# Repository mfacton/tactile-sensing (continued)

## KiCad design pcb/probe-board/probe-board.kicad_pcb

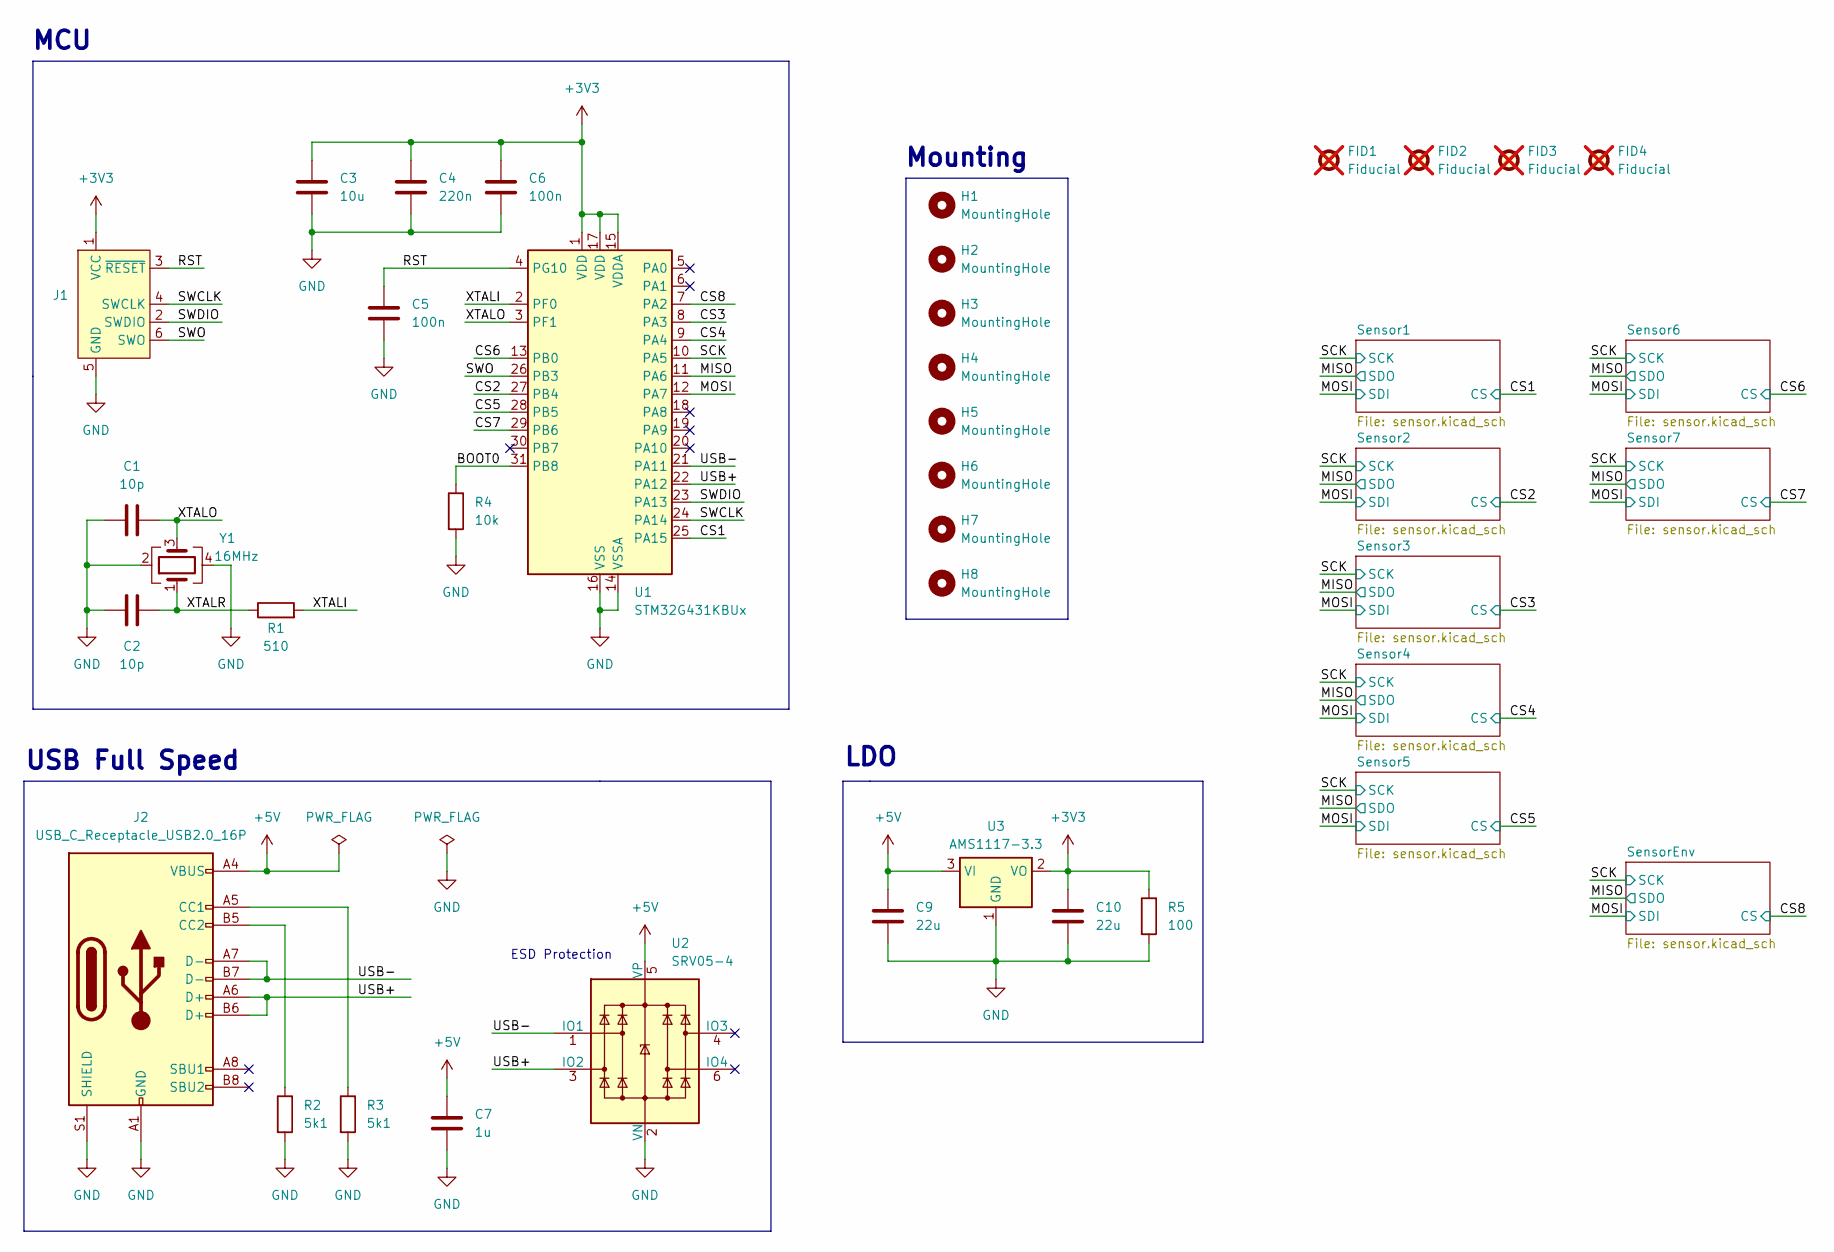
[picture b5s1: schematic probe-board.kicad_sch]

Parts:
C1, C2: 10p; C_0402_1005Metric; LCSC C32949
C3: 10u; C_0402_1005Metric; LCSC C15525
C4: 220n; C_0402_1005Metric; LCSC C16772
C5, C6: 100n; C_0402_1005Metric; LCSC C1525
C7: 1u; C_0402_1005Metric; LCSC C52923
C9: 22u; C_0805_2012Metric; LCSC C45783
C10: 22u; C_0603_1608Metric; LCSC C59461
FID1, FID2, FID3, FID4: Fiducial; Fiducial_1mm_Mask2mm; not fitted
H1, H2, H3, H4, H5, H6, H7, H8: MountingHole; MountingHole_3.2mm_M3
J1: Conn_ARM_SWD_TagConnect_TC2030-NL; Tag-Connect_TC2030-IDC-NL_2x03_P1.27mm_Vertical
J2: USB_C_Receptacle_USB2.0_16P; USB_C_Receptacle_GCT_USB4105-xx-A_16P_TopMnt_Horizontal; LCSC C2765186
R1: 510; R_0402_1005Metric; LCSC C25123
R2, R3: 5k1; R_0402_1005Metric; LCSC C25905
R4: 10k; R_0402_1005Metric; LCSC C25744
R5: 100; R_0805_2012Metric; LCSC C17408
U1: STM32G431KBUx; QFN-32-1EP_5x5mm_P0.5mm_EP3.45x3.45mm; LCSC C1341901
U2: SRV05-4; SOT-23-6; LCSC C7420376
U3: AMS1117-3.3; SOT-223-3_TabPin2; LCSC C6186
Y1: 16MHz; Crystal_SMD_3225-4Pin_3.2x2.5mm; LCSC C13738

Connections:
+3V3: C3.1, C4.1, C6.1, C10.1, J1.1 (VCC), R5.1, U1.1 (VDD), U1.15 (VDDA), U1.17 (VDD), U3.2 (VO); also elsewhere on the board
+5V: C7.1, C9.1, J2.A4 (VBUS), J2.A9 (VBUS), J2.B4 (VBUS), J2.B9 (VBUS), U2.5 (VP), U3.3 (VI)
/BOOT0: R4.1, U1.31 (PB8)
/CS1: U1.25 (PA15); also elsewhere on the board
/CS2: U1.27 (PB4); also elsewhere on the board
/CS3: U1.8 (PA3); also elsewhere on the board
/CS4: U1.9 (PA4); also elsewhere on the board
/CS5: U1.28 (PB5); also elsewhere on the board
/CS6: U1.13 (PB0); also elsewhere on the board
/CS7: U1.29 (PB6); also elsewhere on the board
/CS8: U1.7 (PA2); also elsewhere on the board
/MISO: U1.11 (PA6); also elsewhere on the board
/MOSI: U1.12 (PA7); also elsewhere on the board
/RST: C5.1, J1.3 (~RESET), U1.4 (PG10)
/SCK: U1.10 (PA5); also elsewhere on the board
/SWCLK: J1.4 (SWCLK), U1.24 (PA14)
/SWDIO: J1.2 (SWDIO), U1.23 (PA13)
/SWO: J1.6 (SWO), U1.26 (PB3)
/USB+: J2.A6 (D+), J2.B6 (D+), U1.22 (PA12), U2.3 (IO2)
/USB-: J2.A7 (D-), J2.B7 (D-), U1.21 (PA11), U2.1 (IO1)
/XTALI: R1.2, U1.2 (PF0)
/XTALO: C1.2, U1.3 (PF1), Y1.3
/XTALR: C2.2, R1.1, Y1.1
GND: C1.1, C2.1, C3.2, C4.2, C5.2, C6.2, C7.2, C9.2, C10.2, J1.5 (GND), J2.A1 (GND), J2.A12 (GND), J2.B1 (GND), J2.B12 (GND), J2.S1 (SHIELD), R2.2, R3.2, R4.2, R5.2, U1.14 (VSSA), U1.16 (VSS), U1.32 (VSS), U1.33 (VSS), U2.2 (VN), U3.1 (GND), Y1.2, Y1.4; also elsewhere on the board
unnamed: J2.A5 (CC1), R3.1
unnamed: J2.B5 (CC2), R2.1

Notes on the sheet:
ESD Protection
LDO
MCU
Mounting
USB Full Speed

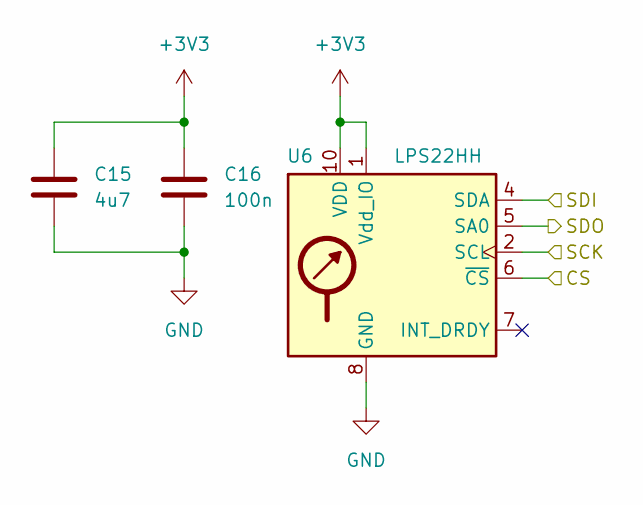
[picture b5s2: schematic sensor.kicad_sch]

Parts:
C15: 4u7; C_0402_1005Metric; LCSC C23733
C16: 100n; C_0402_1005Metric; LCSC C1525
U6: LPS22HH; ST_HLGA-10_2x2mm_P0.5mm_LayoutBorder3x2y; LCSC C2827824

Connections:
+3V3: C15.1, C16.1, U6.1 (Vdd_IO), U6.10 (VDD); also elsewhere on the board
/CS3: U6.6 (~CS); also elsewhere on the board
/MISO: U6.5 (SA0); also elsewhere on the board
/MOSI: U6.4 (SDA); also elsewhere on the board
/SCK: U6.2 (SCL); also elsewhere on the board
GND: C15.2, C16.2, U6.3 (GND), U6.8 (GND), U6.9 (GND); also elsewhere on the board

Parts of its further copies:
C11, C13, C17, C19, C21, C27, C29: 4u7; C_0402_1005Metric; LCSC C23733
C12, C14, C18, C20, C22, C28, C30: 100n; C_0402_1005Metric; LCSC C1525
U4, U5, U7, U8, U9, U12, U13: LPS22HH; ST_HLGA-10_2x2mm_P0.5mm_LayoutBorder3x2y; LCSC C2827824

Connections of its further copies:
+3V3: C11.1, C12.1, C13.1, C14.1, C17.1, C18.1, C19.1, C20.1, C21.1, C22.1, C27.1, C28.1, C29.1, C30.1, U4.1 (Vdd_IO), U4.10 (VDD), U5.1 (Vdd_IO), U5.10 (VDD), U7.1 (Vdd_IO), U7.10 (VDD), U8.1 (Vdd_IO), U8.10 (VDD), U9.1 (Vdd_IO), U9.10 (VDD), U12.1 (Vdd_IO), U12.10 (VDD), U13.1 (Vdd_IO), U13.10 (VDD); also elsewhere on the board
/CS1: U4.6 (~CS); also elsewhere on the board
/CS2: U5.6 (~CS); also elsewhere on the board
/CS4: U7.6 (~CS); also elsewhere on the board
/CS5: U8.6 (~CS); also elsewhere on the board
/CS6: U9.6 (~CS); also elsewhere on the board
/CS7: U12.6 (~CS); also elsewhere on the board
/CS8: U13.6 (~CS); also elsewhere on the board
/MISO: U4.5 (SA0), U5.5 (SA0), U7.5 (SA0), U8.5 (SA0), U9.5 (SA0), U12.5 (SA0), U13.5 (SA0); also elsewhere on the board
/MOSI: U4.4 (SDA), U5.4 (SDA), U7.4 (SDA), U8.4 (SDA), U9.4 (SDA), U12.4 (SDA), U13.4 (SDA); also elsewhere on the board
/SCK: U4.2 (SCL), U5.2 (SCL), U7.2 (SCL), U8.2 (SCL), U9.2 (SCL), U12.2 (SCL), U13.2 (SCL); also elsewhere on the board
GND: C11.2, C12.2, C13.2, C14.2, C17.2, C18.2, C19.2, C20.2, C21.2, C22.2, C27.2, C28.2, C29.2, C30.2, U4.3 (GND), U4.8 (GND), U4.9 (GND), U5.3 (GND), U5.8 (GND), U5.9 (GND), U7.3 (GND), U7.8 (GND), U7.9 (GND), U8.3 (GND), U8.8 (GND), U8.9 (GND), U9.3 (GND), U9.8 (GND), U9.9 (GND), U12.3 (GND), U12.8 (GND), U12.9 (GND), U13.3 (GND), U13.8 (GND), U13.9 (GND); also elsewhere on the board

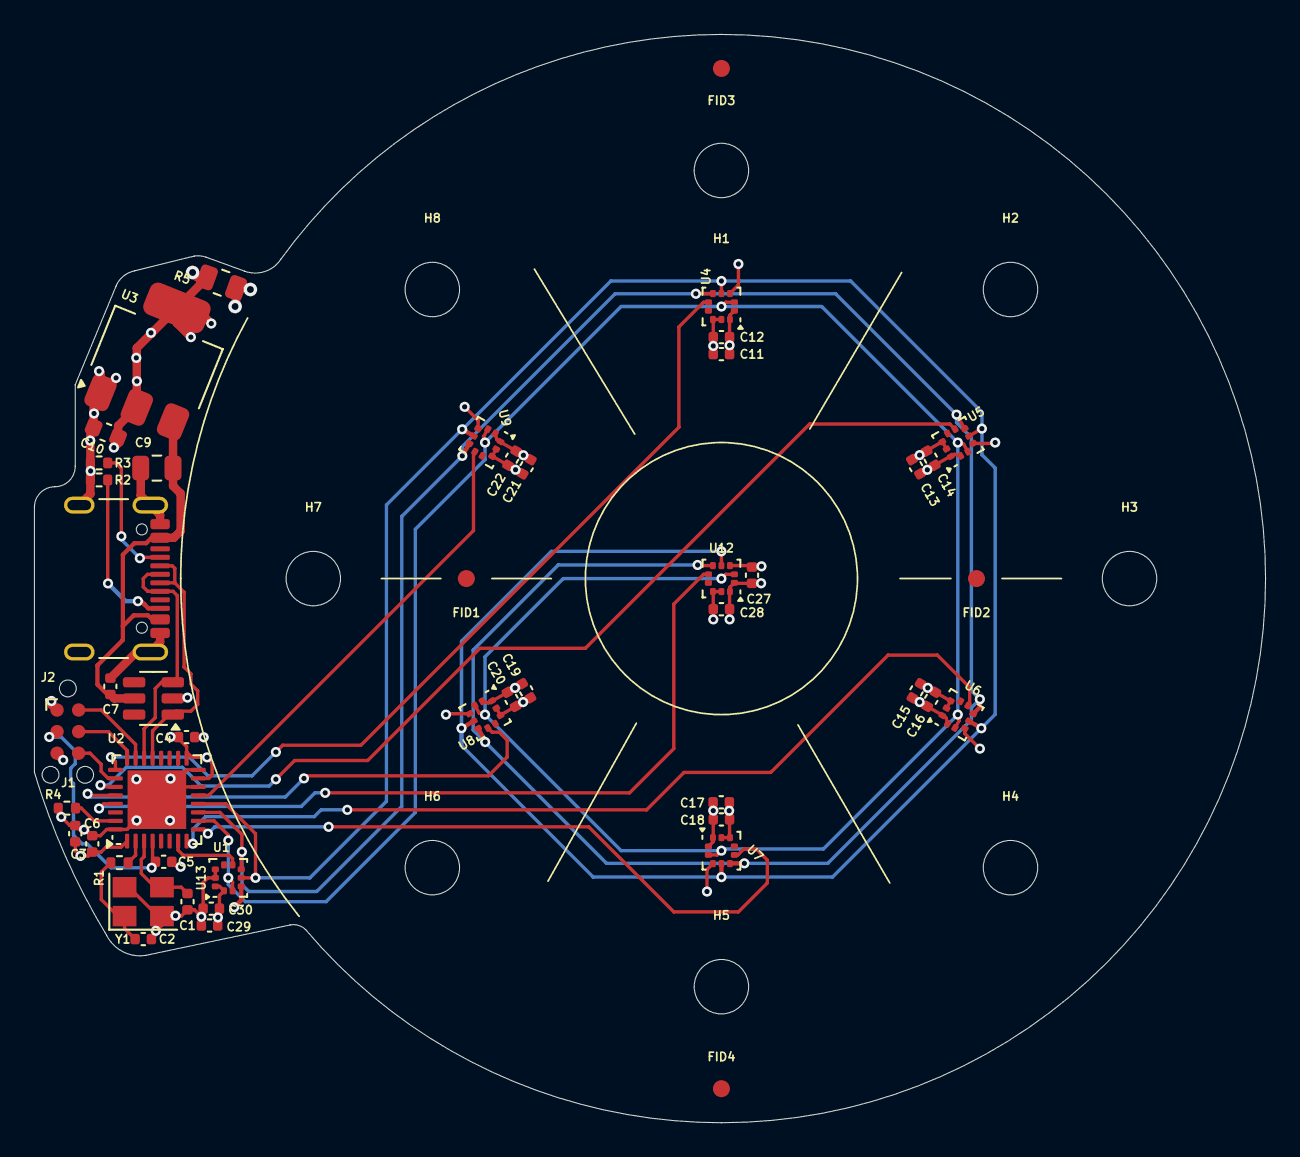
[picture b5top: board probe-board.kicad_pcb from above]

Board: 4 copper layers, 72.4 x 64.0 mm, 56 parts (0 on the bottom side), 26 nets.

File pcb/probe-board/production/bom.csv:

Designator,Footprint,Quantity,Value,LCSC Part #
"C1, C2",0402,2,10p,C32949
C10,0603,1,22u,C59461
"C11, C13, C15, C17, C19, C21, C27, C29",0402,8,4u7,C23733
"C12, C14, C16, C18, C20, C22, C28, C30, C5, C6",0402,10,100n,C1525
C3,0402,1,10u,C15525
C4,0402,1,220n,C16772
C7,0402,1,1u,C52923
C9,0805,1,22u,C45783
J2,USB_C_Receptacle_GCT_USB4105-xx-A_16P_TopMnt_Horizontal,1,USB_C_Receptacle_USB2.0_16P,C2765186
R1,0402,1,510,C25123
"R2, R3",0402,2,5k1,C25905
R4,0402,1,10k,C25744
R5,0805,1,100,C17408
U1,QFN-32-1EP_5x5mm_P0.5mm_EP3.45x3.45mm,1,STM32G431KBUx,C1341901
"U12, U13, U4, U5, U6, U7, U8, U9",ST_HLGA-10_2x2mm_P0.5mm_LayoutBorder3x2y,8,LPS22HH,C2827824
U2,SOT-23-6,1,SRV05-4,C7420376
U3,SOT-223-3_TabPin2,1,AMS1117-3.3,C6186
Y1,Crystal_SMD_3225-4Pin_3.2x2.5mm,1,16MHz,C13738

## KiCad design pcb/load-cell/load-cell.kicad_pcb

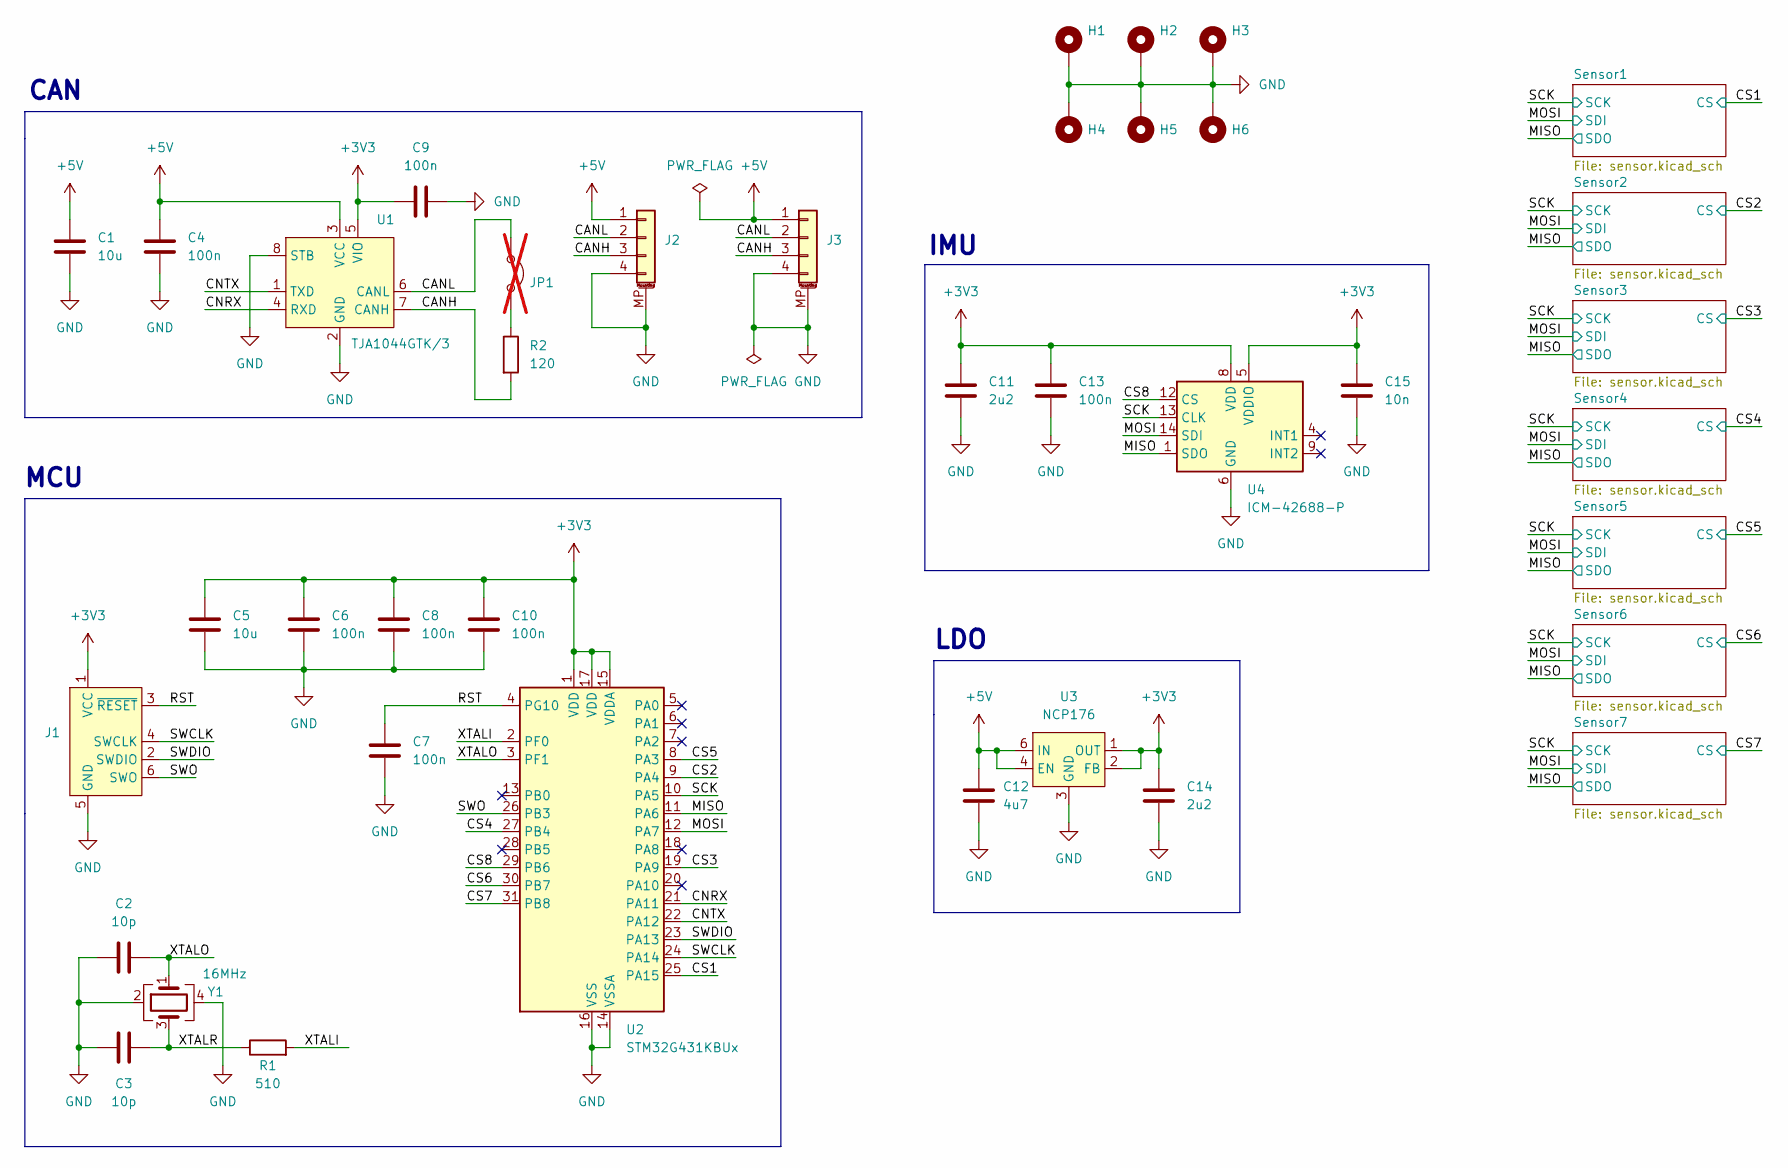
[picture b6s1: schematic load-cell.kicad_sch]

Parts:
C1: 10u; C_0603_1608Metric; LCSC C19702
C2, C3: 10p; C_0402_1005Metric; LCSC C32949
C4, C6, C7, C8, C9, C10, C13: 100n; C_0402_1005Metric; LCSC C1525
C5: 10u; C_0402_1005Metric; LCSC C15525
C11, C14: 2u2; C_0402_1005Metric; LCSC C12530
C12: 4u7; C_0603_1608Metric; LCSC C19666
C15: 10n; C_0402_1005Metric; LCSC C15195
H1, H2, H3, H4, H5, H6: MountingHole_Pad; MountingHole_3.2mm_M3_Pad
J1: Conn_ARM_SWD_TagConnect_TC2030-NL; Tag-Connect_TC2030-IDC-NL_2x03_P1.27mm_Vertical
J2, J3: Conn_01x04_MountingPin; JST_GH_SM04B-GHS-TB_1x04-1MP_P1.25mm_Horizontal; LCSC C189895
JP1: Jumper_2_Open; SolderJumper-2_P1.3mm_Open_RoundedPad1.0x1.5mm; not fitted
R1: 510; R_0402_1005Metric; LCSC C25123
R2: 120; R_1206_3216Metric; LCSC C17909
U1: TJA1044GTK/3; HVSON-8-1EP_3x3mm_P0.65mm_EP1.6x2.4mm; LCSC C2157795
U2: STM32G431KBUx; QFN-32-1EP_5x5mm_P0.5mm_EP3.45x3.45mm; LCSC C1341901
U3: NCP176; DFN-6-1EP_1.2x1.2mm_P0.4mm_EP0.3x0.94mm_PullBack; LCSC C233363
U4: ICM-42688-P; LGA-14_3x2.5mm_P0.5mm_LayoutBorder3x4y; LCSC C1850418
Y1: 16MHz; Crystal_SMD_3225-4Pin_3.2x2.5mm; LCSC C13738

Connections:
+3V3: C5.1, C6.1, C8.1, C9.1, C10.1, C11.1, C13.1, C14.1, C15.1, J1.1 (VCC), U1.5 (VIO), U2.1 (VDD), U2.15 (VDDA), U2.17 (VDD), U3.1 (OUT), U3.2 (FB), U4.5 (VDDIO), U4.8 (VDD); also elsewhere on the board
+5V: C1.1, C4.2, C12.1, J2.1, J3.1, U1.3 (VCC), U3.4 (EN), U3.6 (IN)
/CANH: J2.3, J3.3, R2.2, U1.7 (CANH)
/CANL: J2.2, J3.2, JP1.2 (B), U1.6 (CANL)
/CNRX: U1.4 (RXD), U2.21 (PA11)
/CNTX: U1.1 (TXD), U2.22 (PA12)
/CS1: U2.25 (PA15); also elsewhere on the board
/CS2: U2.9 (PA4); also elsewhere on the board
/CS3: U2.19 (PA9); also elsewhere on the board
/CS4: U2.27 (PB4); also elsewhere on the board
/CS5: U2.8 (PA3); also elsewhere on the board
/CS6: U2.30 (PB7); also elsewhere on the board
/CS7: U2.31 (PB8); also elsewhere on the board
/CS8: U2.29 (PB6), U4.12 (CS)
/MISO: U2.11 (PA6), U4.1 (SDO); also elsewhere on the board
/MOSI: U2.12 (PA7), U4.14 (SDI); also elsewhere on the board
/RST: C7.1, J1.3 (~RESET), U2.4 (PG10)
/SCK: U2.10 (PA5), U4.13 (CLK); also elsewhere on the board
/SWCLK: J1.4 (SWCLK), U2.24 (PA14)
/SWDIO: J1.2 (SWDIO), U2.23 (PA13)
/SWO: J1.6 (SWO), U2.26 (PB3)
/XTALI: R1.2, U2.2 (PF0)
/XTALO: C2.2, U2.3 (PF1), Y1.1
/XTALR: C3.2, R1.1, Y1.3
GND: C1.2, C2.1, C3.1, C4.1, C5.2, C6.2, C7.2, C8.2, C9.2, C10.2, C11.2, C12.2, C13.2, C14.2, C15.2, H1.1, H2.1, H3.1, H4.1, H5.1, H6.1, J1.5 (GND), J2.4, J2.MP (MountPin), J3.4, J3.MP (MountPin), U1.2 (GND), U1.8 (STB), U1.9 (EPAD), U2.14 (VSSA), U2.16 (VSS), U2.32 (VSS), U2.33 (VSS), U3.3 (GND), U3.7 (EPAD), U4.6 (GND), U4.7 (RESV), U4.11 (RESV), Y1.2, Y1.4; also elsewhere on the board
unnamed: JP1.1 (A), R2.1

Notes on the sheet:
IMU
CAN
LDO
MCU

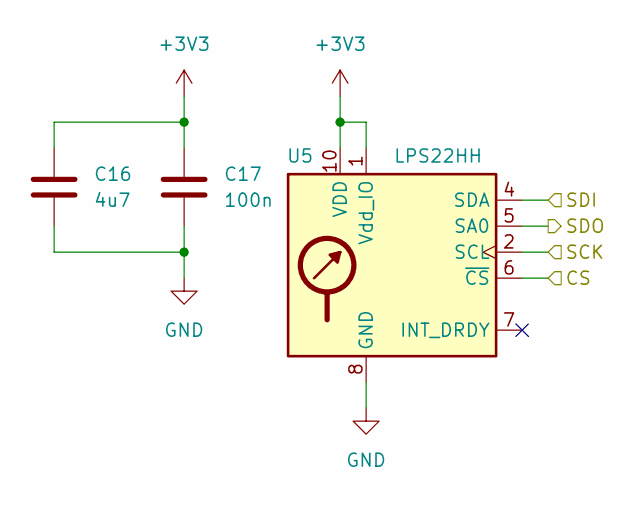
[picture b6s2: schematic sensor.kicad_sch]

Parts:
C16: 4u7; C_0402_1005Metric; LCSC C23733
C17: 100n; C_0402_1005Metric; LCSC C1525
U5: LPS22HH; ST_HLGA-10_2x2mm_P0.5mm_LayoutBorder3x2y; LCSC C2827824

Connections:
+3V3: C16.1, C17.1, U5.1 (Vdd_IO), U5.10 (VDD); also elsewhere on the board
/CS1: U5.6 (~CS); also elsewhere on the board
/MISO: U5.5 (SA0); also elsewhere on the board
/MOSI: U5.4 (SDA); also elsewhere on the board
/SCK: U5.2 (SCL); also elsewhere on the board
GND: C16.2, C17.2, U5.3 (GND), U5.8 (GND), U5.9 (GND); also elsewhere on the board

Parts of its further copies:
C18, C20, C22, C24, C26, C28: 4u7; C_0402_1005Metric; LCSC C23733
C19, C21, C23, C25, C27, C29: 100n; C_0402_1005Metric; LCSC C1525
U6, U7, U8, U9, U10, U11: LPS22HH; ST_HLGA-10_2x2mm_P0.5mm_LayoutBorder3x2y; LCSC C2827824

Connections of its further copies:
+3V3: C18.1, C19.1, C20.1, C21.1, C22.1, C23.1, C24.1, C25.1, C26.1, C27.1, C28.1, C29.1, U6.1 (Vdd_IO), U6.10 (VDD), U7.1 (Vdd_IO), U7.10 (VDD), U8.1 (Vdd_IO), U8.10 (VDD), U9.1 (Vdd_IO), U9.10 (VDD), U10.1 (Vdd_IO), U10.10 (VDD), U11.1 (Vdd_IO), U11.10 (VDD); also elsewhere on the board
/CS2: U6.6 (~CS); also elsewhere on the board
/CS3: U7.6 (~CS); also elsewhere on the board
/CS4: U8.6 (~CS); also elsewhere on the board
/CS5: U9.6 (~CS); also elsewhere on the board
/CS6: U10.6 (~CS); also elsewhere on the board
/CS7: U11.6 (~CS); also elsewhere on the board
/MISO: U6.5 (SA0), U7.5 (SA0), U8.5 (SA0), U9.5 (SA0), U10.5 (SA0), U11.5 (SA0); also elsewhere on the board
/MOSI: U6.4 (SDA), U7.4 (SDA), U8.4 (SDA), U9.4 (SDA), U10.4 (SDA), U11.4 (SDA); also elsewhere on the board
/SCK: U6.2 (SCL), U7.2 (SCL), U8.2 (SCL), U9.2 (SCL), U10.2 (SCL), U11.2 (SCL); also elsewhere on the board
GND: C18.2, C19.2, C20.2, C21.2, C22.2, C23.2, C24.2, C25.2, C26.2, C27.2, C28.2, C29.2, U6.3 (GND), U6.8 (GND), U6.9 (GND), U7.3 (GND), U7.8 (GND), U7.9 (GND), U8.3 (GND), U8.8 (GND), U8.9 (GND), U9.3 (GND), U9.8 (GND), U9.9 (GND), U10.3 (GND), U10.8 (GND), U10.9 (GND), U11.3 (GND), U11.8 (GND), U11.9 (GND); also elsewhere on the board

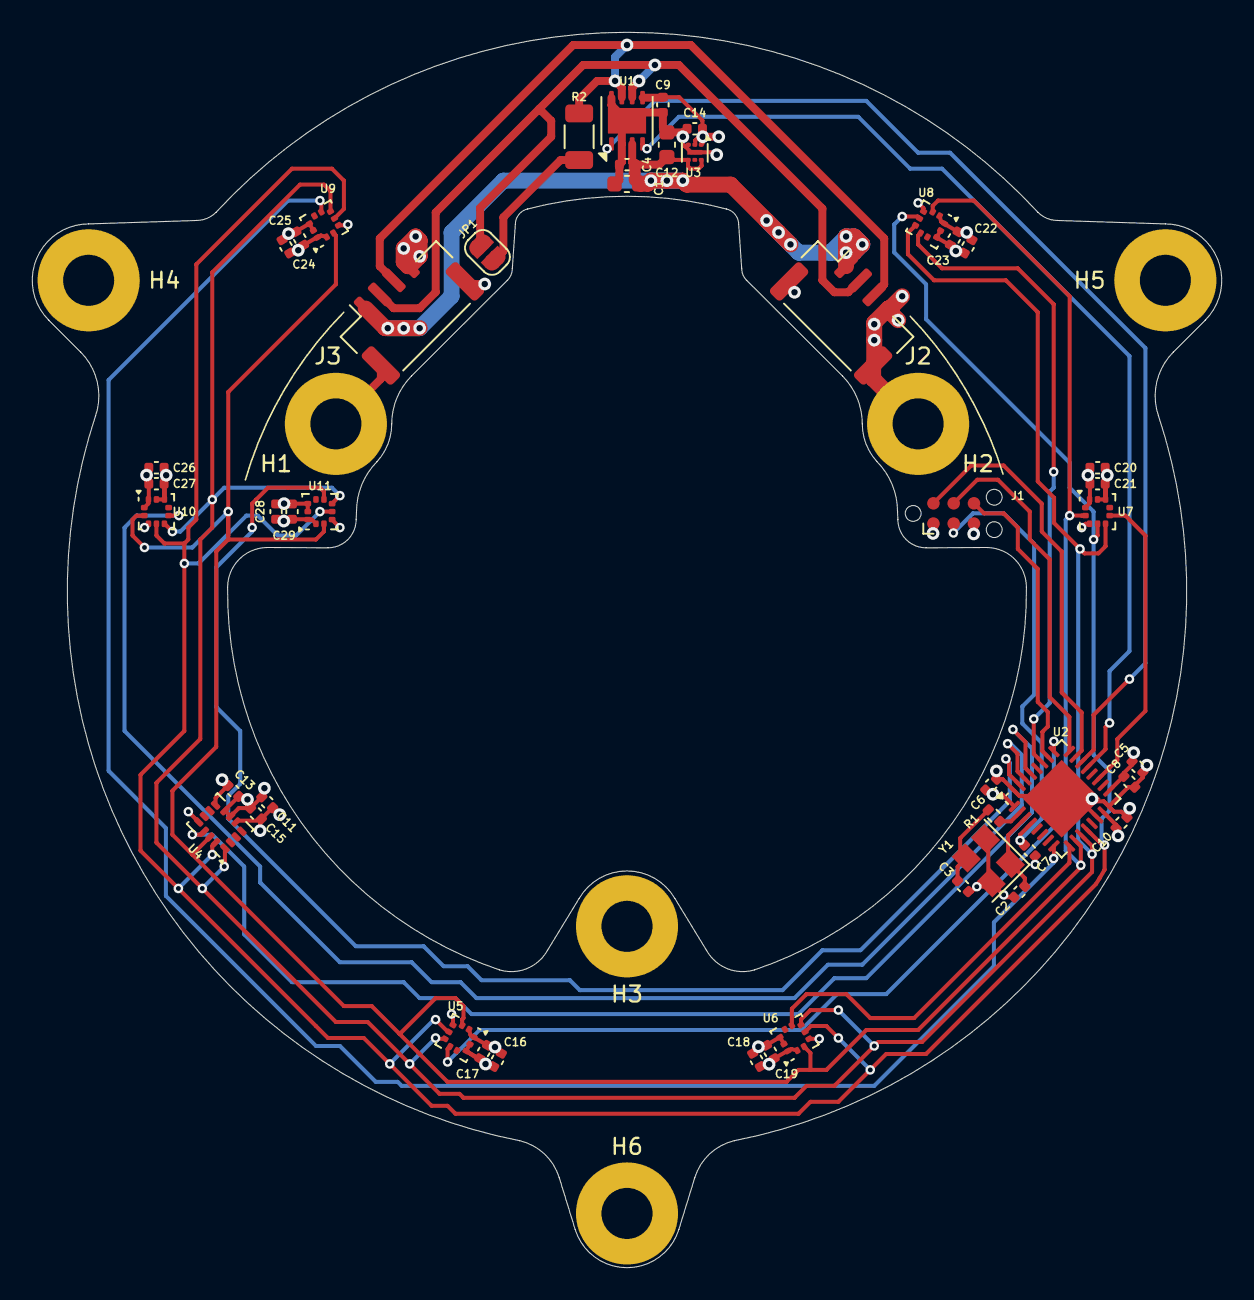
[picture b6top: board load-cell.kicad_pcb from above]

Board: 4 copper layers, 74.6 x 77.4 mm, 54 parts (1 on the bottom side), 26 nets.

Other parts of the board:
G1: LOGO

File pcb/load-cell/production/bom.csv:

Designator,Footprint,Quantity,Value,LCSC Part #
C1,0603,1,10u,C19702
"C10, C13, C17, C19, C21, C23, C25, C27, C29, C4, C6, C7, C8, C9",0402,14,100n,C1525
"C11, C14",0402,2,2u2,C12530
C12,0603,1,4u7,C19666
C15,0402,1,10n,C15195
"C16, C18, C20, C22, C24, C26, C28",0402,7,4u7,C23733
"C2, C3",0402,2,10p,C32949
C5,0402,1,10u,C15525
"J2, J3",JST_GH_SM04B-GHS-TB_1x04-1MP_P1.25mm_Horizontal,2,Conn_01x04_MountingPin,C189895
R1,0402,1,510,C25123
R2,1206,1,120,C17909
U1,HVSON-8-1EP_3x3mm_P0.65mm_EP1.6x2.4mm,1,TJA1044GTK/3,C2157795
"U10, U11, U5, U6, U7, U8, U9",ST_HLGA-10_2x2mm_P0.5mm_LayoutBorder3x2y,7,LPS22HH,C2827824
U2,QFN-32-1EP_5x5mm_P0.5mm_EP3.45x3.45mm,1,STM32G431KBUx,C1341901
U3,DFN-6-1EP_1.2x1.2mm_P0.4mm_EP0.3x0.94mm_PullBack,1,NCP176,C233363
U4,LGA-14_3x2.5mm_P0.5mm_LayoutBorder3x4y,1,ICM-42688-P,C1850418
Y1,Crystal_SMD_3225-4Pin_3.2x2.5mm,1,16MHz,C13738

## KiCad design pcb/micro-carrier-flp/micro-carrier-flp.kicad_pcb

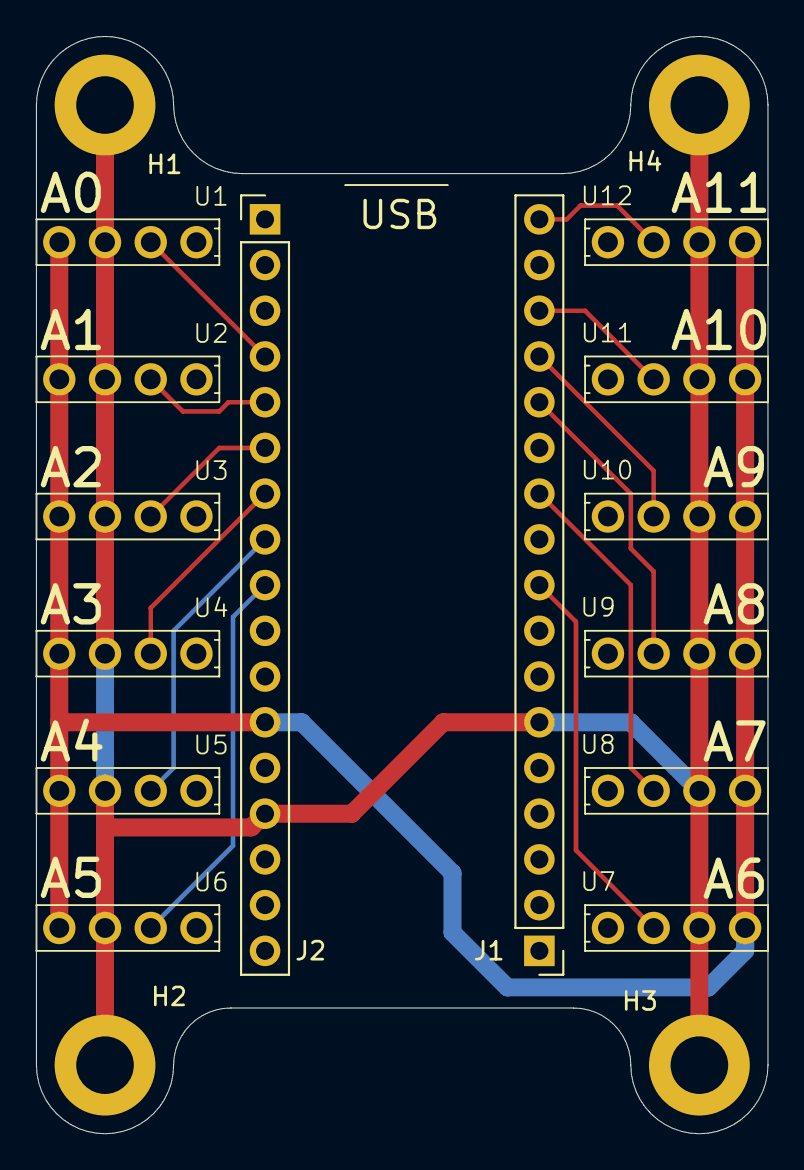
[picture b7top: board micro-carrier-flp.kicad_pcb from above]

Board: 2 copper layers, 40.6 x 61.0 mm, 18 parts (0 on the bottom side), 14 nets.

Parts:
H1, H2, H3, H4: MountingHole_Pad; MountingHole_3.2mm_M3_DIN965_Pad
J1, J2: Conn_01x17; PinHeader_1x17_P2.54mm_Vertical
U1, U2, U3, U4, U5, U6, U7, U8, U9, U10, U11, U12: P4V-MINI

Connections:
+5V: J2.12, U1.4 (5V), U2.4 (5V), U3.4 (5V), U4.4 (5V), U5.4 (5V), U6.4 (5V), U7.4 (5V), U8.4 (5V), U9.4 (5V), U10.4 (5V), U11.4 (5V), U12.4 (5V)
/OUT1: J2.4, U1.2 (OUT)
/OUT2: J2.5, U2.2 (OUT)
/OUT3: J2.6, U3.2 (OUT)
/OUT4: J2.7, U4.2 (OUT)
/OUT5: J2.8, U5.2 (OUT)
/OUT6: J2.9, U6.2 (OUT)
/OUT7: J1.9, U7.2 (OUT)
/OUT8: J1.11, U8.2 (OUT)
/OUT9: J1.13, U9.2 (OUT)
/OUT10: J1.14, U10.2 (OUT)
/OUT11: J1.15, U11.2 (OUT)
/OUT12: J1.17, U12.2 (OUT)
GND: H1.1, H2.1, H3.1, H4.1, J1.6, J2.14, U1.3 (GND), U2.3 (GND), U3.3 (GND), U4.3 (GND), U5.3 (GND), U6.3 (GND), U7.3 (GND), U8.3 (GND), U9.3 (GND), U10.3 (GND), U11.3 (GND), U12.3 (GND)

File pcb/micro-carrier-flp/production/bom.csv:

Designator,Footprint,Quantity,Value,LCSC Part #
"J1, J2",PinHeader_1x17_P2.54mm_Vertical,2,Conn_01x17,
"U1, U10, U11, U12, U2, U3, U4, U5, U6, U7, U8, U9",P4V-MINI,12,P4V-MINI,

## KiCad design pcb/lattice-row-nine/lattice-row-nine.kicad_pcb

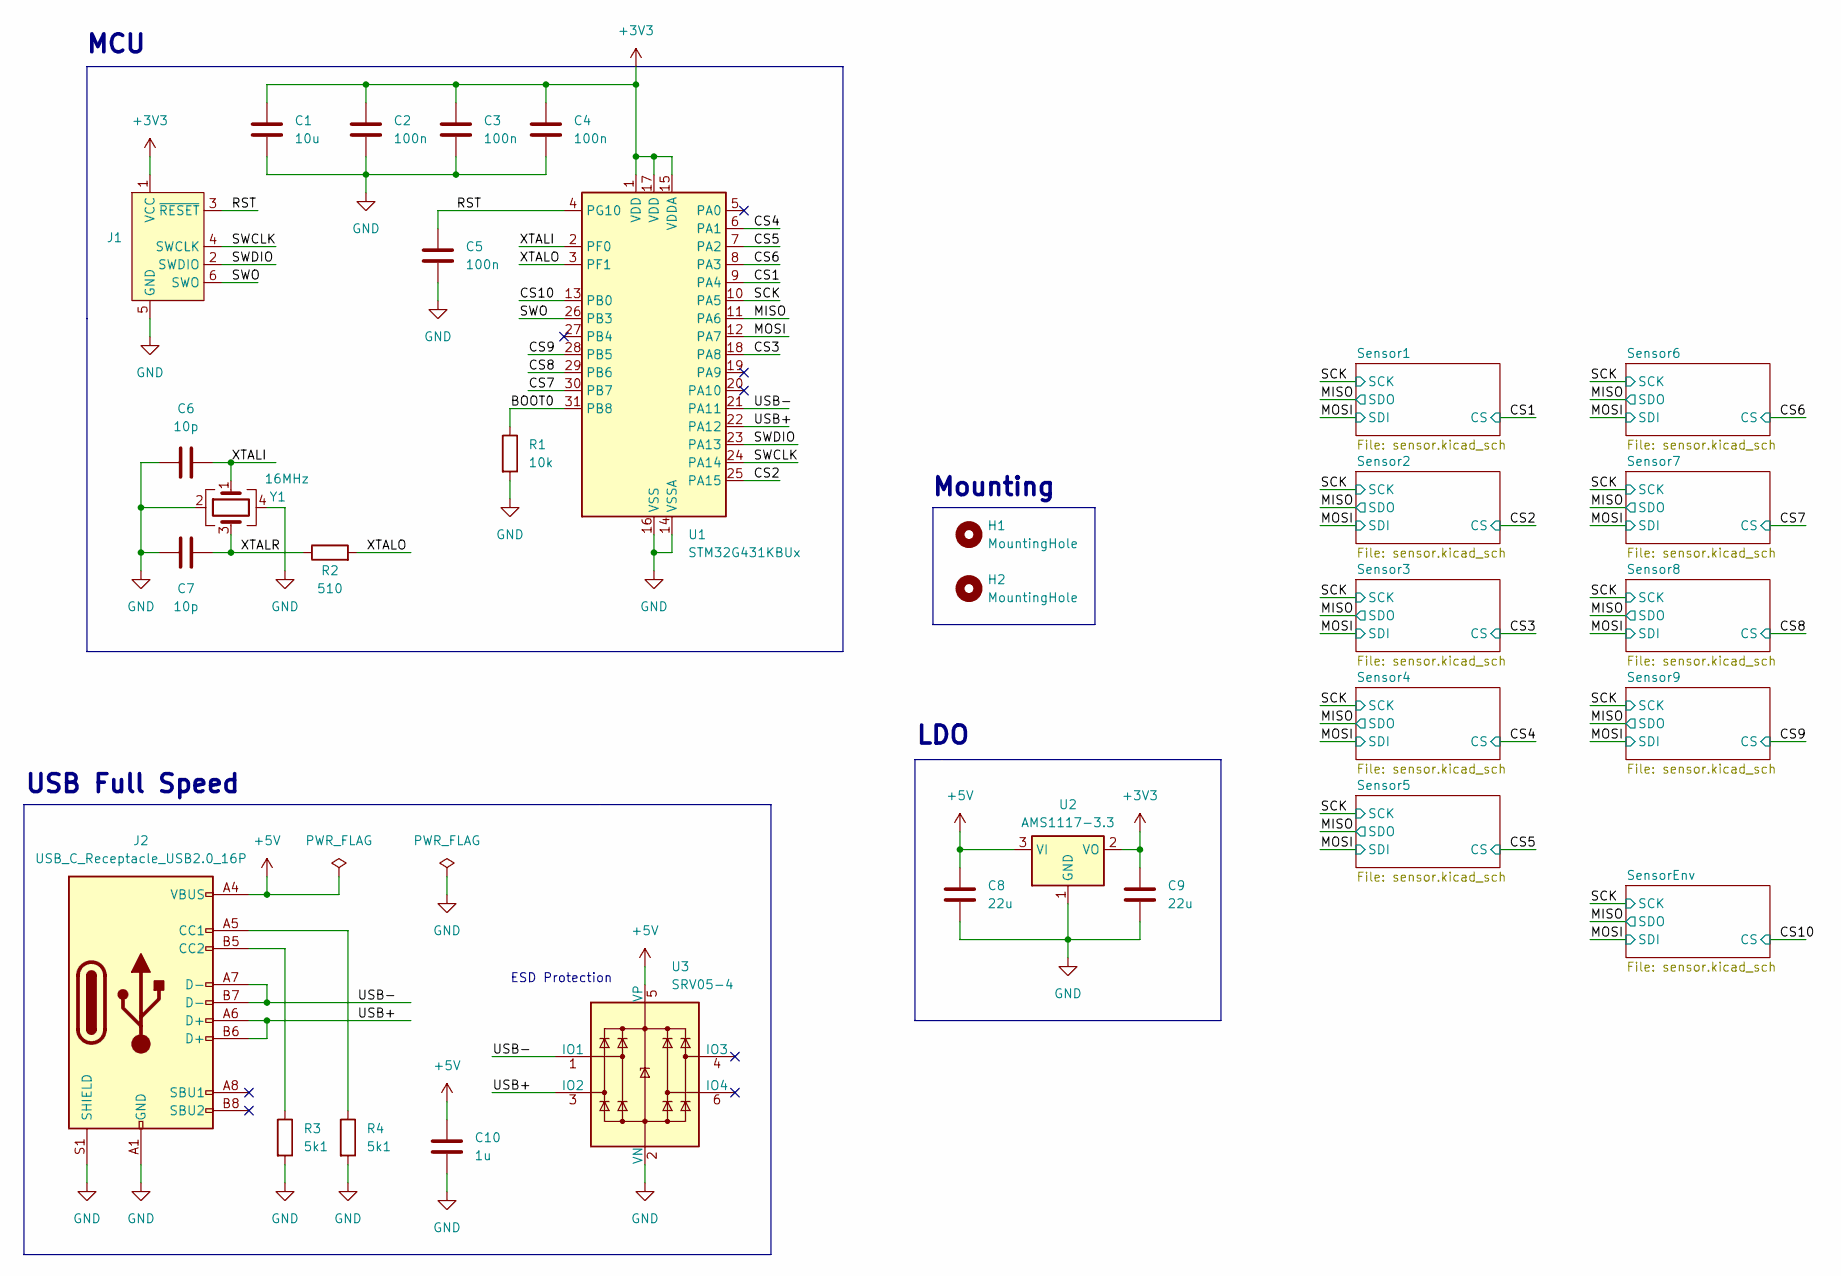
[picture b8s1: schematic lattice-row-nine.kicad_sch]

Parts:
C1: 10u; C_0402_1005Metric; LCSC C15525
C2, C3, C4, C5: 100n; C_0402_1005Metric; LCSC C1525
C6, C7: 10p; C_0402_1005Metric; LCSC C32949
C8: 22u; C_0805_2012Metric; LCSC C45783
C9: 22u; C_0603_1608Metric; LCSC C59461
C10: 1u; C_0402_1005Metric; LCSC C52923
H1, H2: MountingHole; MountingHole_3.2mm_M3
J1: Conn_ARM_SWD_TagConnect_TC2030-NL; Tag-Connect_TC2030-IDC-NL_2x03_P1.27mm_Vertical
J2: USB_C_Receptacle_USB2.0_16P; USB_C_Receptacle_GCT_USB4105-xx-A_16P_TopMnt_Horizontal; LCSC C2765186
R1: 10k; R_0402_1005Metric; LCSC C25744
R2: 510; R_0402_1005Metric; LCSC C25123
R3, R4: 5k1; R_0402_1005Metric; LCSC C25905
U1: STM32G431KBUx; QFN-32-1EP_5x5mm_P0.5mm_EP3.45x3.45mm; LCSC C1341901
U2: AMS1117-3.3; SOT-223-3_TabPin2; LCSC C6186
U3: SRV05-4; SOT-23-6; LCSC C7420376
Y1: 16MHz; Crystal_SMD_3225-4Pin_3.2x2.5mm; LCSC C13738

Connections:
+3V3: C1.1, C2.1, C3.1, C4.1, C9.1, J1.1 (VCC), U1.1 (VDD), U1.15 (VDDA), U1.17 (VDD), U2.2 (VO); also elsewhere on the board
+5V: C8.1, C10.1, J2.A4 (VBUS), J2.A9 (VBUS), J2.B4 (VBUS), J2.B9 (VBUS), U2.3 (VI), U3.5 (VP)
/BOOT0: R1.1, U1.31 (PB8)
/CS1: U1.9 (PA4); also elsewhere on the board
/CS2: U1.25 (PA15); also elsewhere on the board
/CS3: U1.18 (PA8); also elsewhere on the board
/CS4: U1.6 (PA1); also elsewhere on the board
/CS5: U1.7 (PA2); also elsewhere on the board
/CS6: U1.8 (PA3); also elsewhere on the board
/CS7: U1.30 (PB7); also elsewhere on the board
/CS8: U1.29 (PB6); also elsewhere on the board
/CS9: U1.28 (PB5); also elsewhere on the board
/CS10: U1.13 (PB0); also elsewhere on the board
/MISO: U1.11 (PA6); also elsewhere on the board
/MOSI: U1.12 (PA7); also elsewhere on the board
/RST: C5.1, J1.3 (~RESET), U1.4 (PG10)
/SCK: U1.10 (PA5); also elsewhere on the board
/SWCLK: J1.4 (SWCLK), U1.24 (PA14)
/SWDIO: J1.2 (SWDIO), U1.23 (PA13)
/SWO: J1.6 (SWO), U1.26 (PB3)
/USB+: J2.A6 (D+), J2.B6 (D+), U1.22 (PA12), U3.3 (IO2)
/USB-: J2.A7 (D-), J2.B7 (D-), U1.21 (PA11), U3.1 (IO1)
/XTALI: C6.2, U1.2 (PF0), Y1.1
/XTALO: R2.2, U1.3 (PF1)
/XTALR: C7.2, R2.1, Y1.3
GND: C1.2, C2.2, C3.2, C4.2, C5.2, C6.1, C7.1, C8.2, C9.2, C10.2, J1.5 (GND), J2.A1 (GND), J2.A12 (GND), J2.B1 (GND), J2.B12 (GND), J2.S1 (SHIELD), R1.2, R3.2, R4.2, U1.14 (VSSA), U1.16 (VSS), U1.32 (VSS), U1.33 (VSS), U2.1 (GND), U3.2 (VN), Y1.2, Y1.4; also elsewhere on the board
unnamed: J2.A5 (CC1), R4.1
unnamed: J2.B5 (CC2), R3.1

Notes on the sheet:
ESD Protection
MCU
USB Full Speed
Mounting
LDO

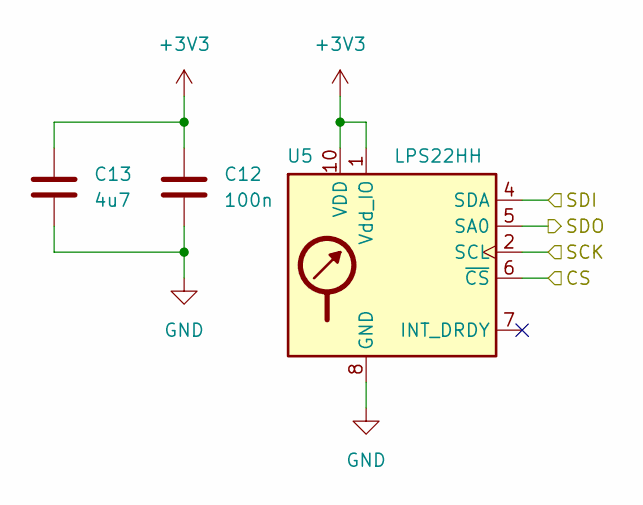
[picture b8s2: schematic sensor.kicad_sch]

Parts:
C12: 100n; C_0402_1005Metric; LCSC C1525
C13: 4u7; C_0402_1005Metric; LCSC C23733
U5: LPS22HH; ST_HLGA-10_2x2mm_P0.5mm_LayoutBorder3x2y; LCSC C2827824

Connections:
+3V3: C12.1, C13.1, U5.1 (Vdd_IO), U5.10 (VDD); also elsewhere on the board
/CS2: U5.6 (~CS); also elsewhere on the board
/MISO: U5.5 (SA0); also elsewhere on the board
/MOSI: U5.4 (SDA); also elsewhere on the board
/SCK: U5.2 (SCL); also elsewhere on the board
GND: C12.2, C13.2, U5.3 (GND), U5.8 (GND), U5.9 (GND); also elsewhere on the board

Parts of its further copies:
C11, C15, C17, C19, C21, C23, C25, C27, C29: 4u7; C_0402_1005Metric; LCSC C23733
C14, C16, C18, C20, C22, C24, C26, C28, C30: 100n; C_0402_1005Metric; LCSC C1525
U4, U6, U7, U8, U9, U10, U11, U12, U13: LPS22HH; ST_HLGA-10_2x2mm_P0.5mm_LayoutBorder3x2y; LCSC C2827824

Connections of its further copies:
+3V3: C11.1, C14.1, C15.1, C16.1, C17.1, C18.1, C19.1, C20.1, C21.1, C22.1, C23.1, C24.1, C25.1, C26.1, C27.1, C28.1, C29.1, C30.1, U4.1 (Vdd_IO), U4.10 (VDD), U6.1 (Vdd_IO), U6.10 (VDD), U7.1 (Vdd_IO), U7.10 (VDD), U8.1 (Vdd_IO), U8.10 (VDD), U9.1 (Vdd_IO), U9.10 (VDD), U10.1 (Vdd_IO), U10.10 (VDD), U11.1 (Vdd_IO), U11.10 (VDD), U12.1 (Vdd_IO), U12.10 (VDD), U13.1 (Vdd_IO), U13.10 (VDD); also elsewhere on the board
/CS1: U4.6 (~CS); also elsewhere on the board
/CS3: U6.6 (~CS); also elsewhere on the board
/CS4: U7.6 (~CS); also elsewhere on the board
/CS5: U8.6 (~CS); also elsewhere on the board
/CS6: U9.6 (~CS); also elsewhere on the board
/CS7: U10.6 (~CS); also elsewhere on the board
/CS8: U11.6 (~CS); also elsewhere on the board
/CS9: U12.6 (~CS); also elsewhere on the board
/CS10: U13.6 (~CS); also elsewhere on the board
/MISO: U4.5 (SA0), U6.5 (SA0), U7.5 (SA0), U8.5 (SA0), U9.5 (SA0), U10.5 (SA0), U11.5 (SA0), U12.5 (SA0), U13.5 (SA0); also elsewhere on the board
/MOSI: U4.4 (SDA), U6.4 (SDA), U7.4 (SDA), U8.4 (SDA), U9.4 (SDA), U10.4 (SDA), U11.4 (SDA), U12.4 (SDA), U13.4 (SDA); also elsewhere on the board
/SCK: U4.2 (SCL), U6.2 (SCL), U7.2 (SCL), U8.2 (SCL), U9.2 (SCL), U10.2 (SCL), U11.2 (SCL), U12.2 (SCL), U13.2 (SCL); also elsewhere on the board
GND: C11.2, C14.2, C15.2, C16.2, C17.2, C18.2, C19.2, C20.2, C21.2, C22.2, C23.2, C24.2, C25.2, C26.2, C27.2, C28.2, C29.2, C30.2, U4.3 (GND), U4.8 (GND), U4.9 (GND), U6.3 (GND), U6.8 (GND), U6.9 (GND), U7.3 (GND), U7.8 (GND), U7.9 (GND), U8.3 (GND), U8.8 (GND), U8.9 (GND), U9.3 (GND), U9.8 (GND), U9.9 (GND), U10.3 (GND), U10.8 (GND), U10.9 (GND), U11.3 (GND), U11.8 (GND), U11.9 (GND), U12.3 (GND), U12.8 (GND), U12.9 (GND), U13.3 (GND), U13.8 (GND), U13.9 (GND); also elsewhere on the board
